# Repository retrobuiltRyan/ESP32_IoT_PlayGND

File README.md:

# ESP32_IoT_PlayGND
Internet of Things + MQTT sensor, input, actuator, motor drive learning board. Can be powered with a power drill battery for immediate remote deployment and sensor monitoring.

Learning Goal: Quick start "how to" develop and build your own IIoT solution with scale and affordability in mind using off-the-shelf hardware and lightweight software.

# Hardware Rev 1.0

| Category       | Components                                                                 |
|----------------|----------------------------------------------------------------------------|
| **Microcontroller** | ESP32-WROOM-32                                                        |
| **Sensors/Input**   | - Temperature & Humidity (SHT45) <br> - Voltage, Current, Power (INA260) <br> - Pushbutton (x4) <br> - Rotary Encoder |
| **Actuators**       | - Relay (10A, 277VAC, 30VDC) <br> - DRV8871 (DC Motor Drive) <br> - A4988 (Stepper Motor Drive) <br> - 4 CH Servo (PCA9685) |
| **Output**          | - RGB LED (x4) <br> - OLED (128x64 pixel) <br> - Buzzer |

ESP-WROOM-32 ESP32: https://www.amazon.com/gp/product/B0D8Q8XFRK/ <br>
USB Drivers for FTDI chips https://docs.espressif.com/projects/esp-idf/en/stable/esp32/get-started/establish-serial-connection.html

BoM
## Bill of Materials (BOM)
| Reference                                                                 | Value                   | Qty | DigiKey P/N               | Adafruit P/N | AliExpress / Amazon Link                                                                 |
|---------------------------------------------------------------------------|-------------------------|-----|---------------------------|--------------|------------------------------------------------------------------------------------------|
| BZ1                                                                       | Buzzer_5V               | 1   | 445-2525-1-ND             |              |                                                                                          |
| C3, C4, C7                                                                | 0.1uF 50V               | 3   | 1276-1068-1-ND            |              |                                                                                          |
| C10, C11                                                                  | 0.22uF 50V CER          | 2   | 445-2283-1-ND             |              |                                                                                          |
| C12, C13, C14                                                             | 22uF 50V                | 3   | 399-11438-1-ND            |              |                                                                                          |
| D2                                                                        | D                       | 1   | S5AC-FDICT-ND             |              |                                                                                          |
| D3, D6, D7, D8                                                            | WS2812B                 | 4   |1568-16347CT-ND            |              |[Aliexpress Link](https://www.aliexpress.us/item/3256802466699315.html)                   |
| D5, D9, D11, D13                                                          | LED, Green              | 3   |1080-1419-1-ND             |              |                                                                                          |
| D10                                                                       | LED Red, 5mm            | 1   | EALP05RDHRA2-ND           |              |                                                                                          |
| D12                                                                       | SMF15A                  | 1   | SMF15A-E3-08CT-ND         |              |                                                                                          |
| D14                                                                       | 1N4148W                 | 1   | 4878-1N4148WCT-ND         |              |                                                                                          |
| J3                                                                        | ServoPort_04            | 1   | S1012EC-40-ND             |              |                                                                                          |
| J5, J8                                                                    | Screw_Terminal_2_P3.50mm| 2   | 732-2747-ND               |              |                                                                                          |
| J7                                                                        | PINHD_2x3_Male          | 1   | S1012EC-40-ND             |              |                                                                                          |
| J15                                                                       | Screw_Terminal_3_P5.00mm| 1   | 277-1578-ND               |              |                                                                                          |
| K1                                                                        | G5Q-1                   | 1   | Z2929-ND                  |              |                                                                                          |
| Q1                                                                        | MOSFET P-CH 30V 25A TO252| 1  | 785-1106-1-ND             |              |                                                                                          |
| Q2, Q3                                                                    | MMBT2222A               | 2   | MMBT2222ATPMSCT-ND        |              |                                                                                          |
| R1, R2, R8, R22, R25, R26, R27, R28, R30, R34, R35, R36, R37, R38         | 10K                     | 14  | 311-10.0KFRCT-ND          |              |                                                                                          |
| R3, R4, R5, R6, R7, R9, R16, R23                                          | 220                     | 8   | 311-220FRCT-ND            |              |                                                                                          |
| R17, R21, R31                                                             | 330                     | 3   | 311-330FRCT-ND            |              |                                                                                          |
| R18, R19, R20, R32                                                        | 1K                      | 4   | 311-1.00KFRCT-ND          |              |                                                                                          |
| R33                                                                       | 100k                    | 1   | 311-100KFRCT-ND           |              |                                                                                          |
| S1                                                                        | SPDT Switch             | 1   | EG5617-ND                 |              |                                                                                          |
| SW1, SW2, SW3, SW4                                                        | Push_Button             | 4   | 2223-TS02-66-60-BK-160-LCR-D-ND |        |                                                                                          |
| SW6                                                                       | RotaryEncoder_Switch_MP | 1   | PEC11R-4220F-S0024-ND     |              |                                                                                          |
| U3                                                                        | PCA9685PW               | 1   | 568-11925-1-ND            |              |                                                                                          |
| U4                                                                        | SHT45                   | 1   |                           | 6174         |                                                                                          |
| U7                                                                        | A4988                   | 1   |                           | 6109         |                                                                                          |
| U8                                                                        | INA260                  | 1   |                           | 4226         |                                                                                          |
| U14                                                                       | MAX40200AUK             | 1   | 175-MAX40203AUK+TCT-ND    |              |                                                                                          |
| U15                                                                       | L7805                   | 1   | 497-7255-1-ND             |              |                                                                                          |
| U18, U19                                                                  | MP1584                  | 2   |                           |              | [AliExpress Link](https://www.aliexpress.us/item/3256806890547813.html)                  |
| U21                                                                       | ESP32                   | 1   |                           |              | [Amazon Link](https://www.amazon.com/gp/product/B0D8Q8XFRK/) _(beware pinout)_            |

## Misc 
Try calling these in a desktop web browser for weather forecast in string format:

*main call*
https://api.weather.gov/points/40.4406,-79.9959

*hourly forecast call*
https://api.weather.gov/gridpoints/PBZ/78,66/forecast/hourly

*weekly forecast*
https://api.weather.gov/gridpoints/PBZ/78,66/forecast

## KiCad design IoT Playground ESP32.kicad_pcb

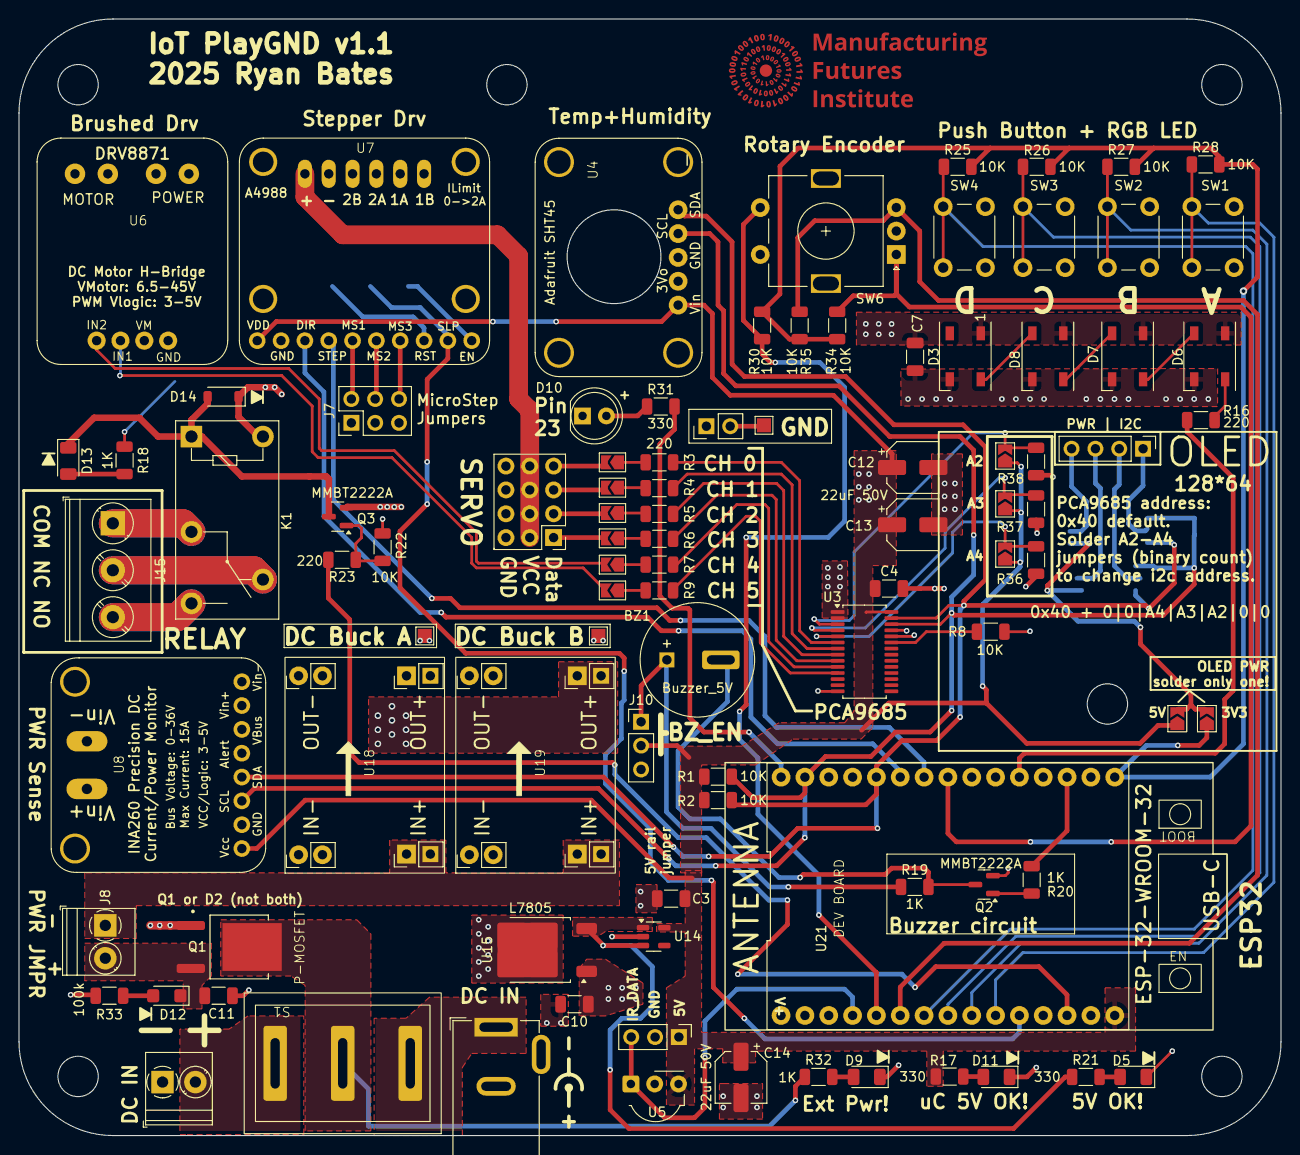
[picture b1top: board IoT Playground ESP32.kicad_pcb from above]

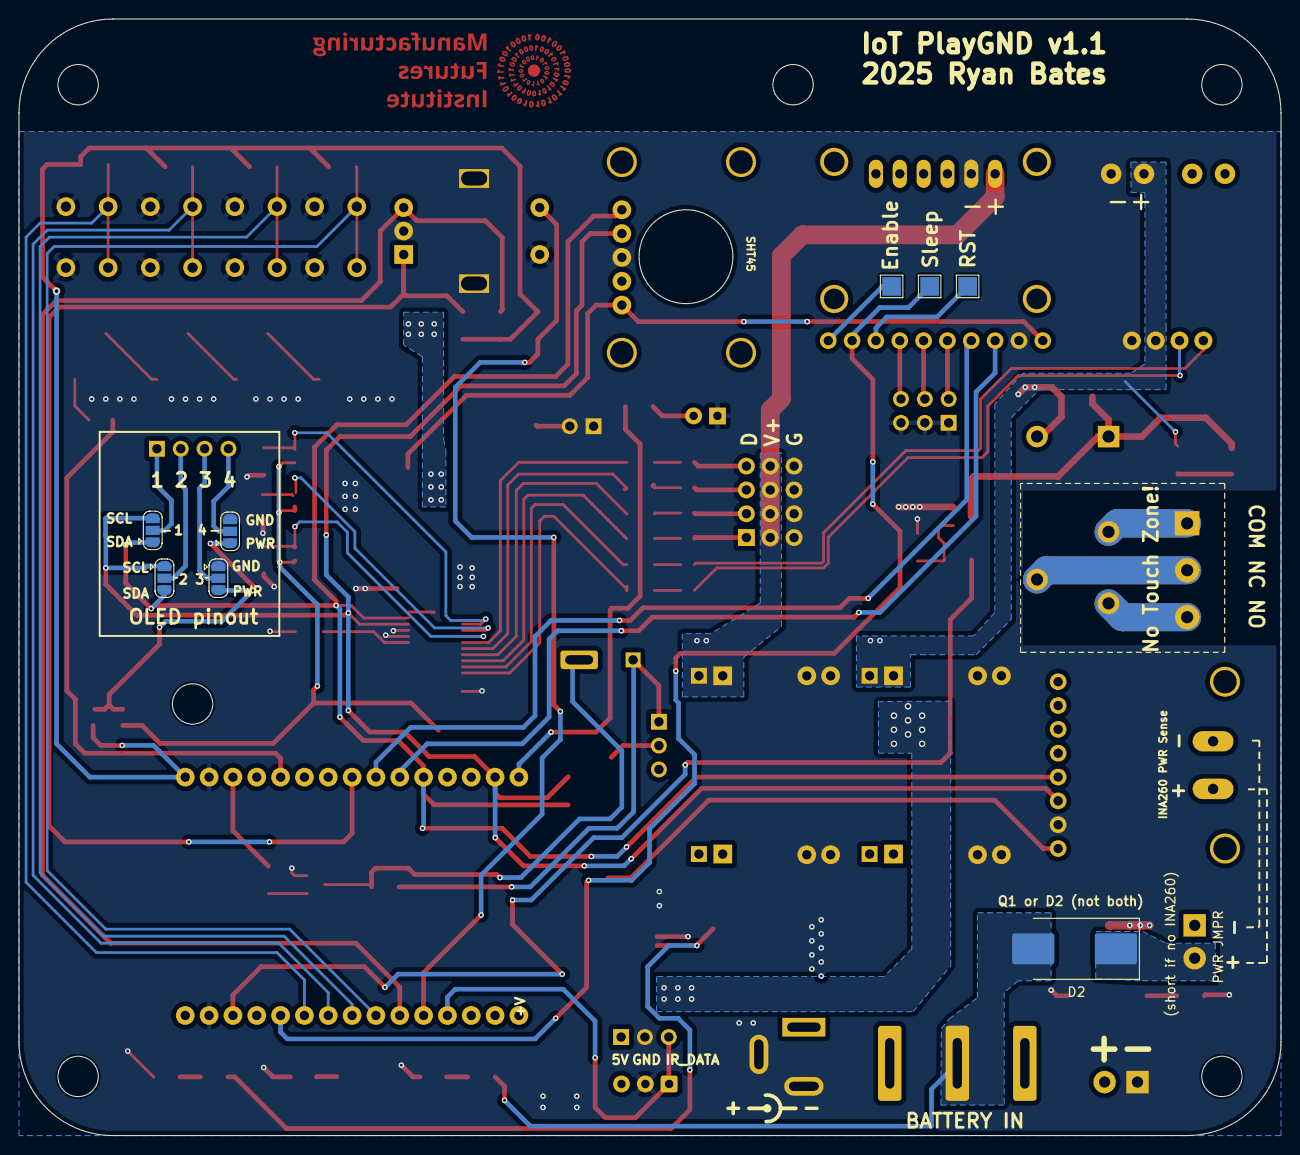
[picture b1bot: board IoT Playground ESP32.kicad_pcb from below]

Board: 2 copper layers, 134.5 x 119.0 mm, 109 parts (8 on the bottom side), 78 nets.

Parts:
BZ1: Buzzer_5V; MagneticBuzzer_ProSignal_ABT-410-RC
C3, C4, C7: 0.1uF 50V; C_1206_3216Metric
C10, C11: 0.22uF 50V CER; C_1206_3216Metric
C12, C13, C14: 22uF 50V; CP_Elec_5x5.3
D2: D; D_SMC_Handsoldering
D3, D6, D7, D8: WS2812B; LED_WS2812B_PLCC4_5.0x5.0mm_P3.2mm
D5, D9, D11, D13: LED; LED_1206_3216Metric
D10: LED; LED_D5.0mm
D12: SMF15A; D_SMF
D14: 1N4148W; D_SOD-123
H1, H2, H3, H4, H5, H6: MountingHole; MountingHole_4.3mm_M4
J1: PINHD_1x2_Male; PinHeader_1x02_P2.54mm_Vertical
J3: ServoPort_04; ServoPort_04_Vertical
J4, J10: PINHD_1x3_Male; PinHeader_1x03_P2.54mm_Vertical
J5, J8: Screw_Terminal_2_P3.50mm; TerminalBlock_Phoenix_PT-1,5-2-3.5-H_1x02_P3.50mm_Horizontal
J6: PINHD_1x4_Male; PinHeader_1x04_P2.54mm_Vertical
J7: PINHD_2x3_Male; PinHeader_2x03_P2.54mm_Vertical
J9: Barrel_Jack; BarrelJack_GCT_DCJ200-10-A_Horizontal
J15: Screw_Terminal_3_P5.00mm; TerminalBlock_Phoenix_PT-1,5-3-5.0-H_1x03_P5.00mm_Horizontal
JP1, JP2, JP3, JP4, JP5, JP6, JP9, JP10, JP13, JP14, JP15: SolderJumper_2_Open; SolderJumper-2_P1.3mm_Open_TrianglePad1.0x1.5mm
JP7, JP8, JP11, JP12: SolderJumper_3_Open; SolderJumper-3_P1.3mm_Open_RoundedPad1.0x1.5mm
K1: G5Q-1; Relay_SPDT_Omron-G5Q-1
Q1: MOSFET P-CH 30V 25A TO252; MOSFET_P-CH_30V_25A_TO252
Q2, Q3: MMBT2222A; SOT-23
R1, R2, R8, R22, R25, R26, R27, R28, R30, R34, R35, R36, R37, R38: 10K; R_1206_3216Metric
R3, R4, R5, R6, R7, R9, R16, R23: 220; R_1206_3216Metric
R17, R21, R31: 330; R_1206_3216Metric
R18, R19, R20, R32: 1K; R_1206_3216Metric
R33: 100k; R_1206_3216Metric
S1: SPDT Switch; SPDT_ Rocker_Switch
SW1, SW2, SW3, SW4: Push_Button; SW_PUSH_6mm
SW6: RotaryEncoder_Switch_MP; RotaryEncoder_Alps_EC11E-Switch_Vertical_H20mm
TP2, TP8, TP9: TestPoint; TestPoint_Pad_2.0x2.0mm
TP10, TP11, TP12: TestPoint; TestPoint_Pad_1.5x1.5mm
U3: PCA9685PW; TSSOP-28_4.4x9.7mm_P0.65mm
U4: SHT45; Adafruit SHT45
U5: TSDP341xx; Vishay_MOLD-3Pin
U6: DRV8871; DRV8871_Adafruit
U7: A4988; Adafruit A4988
U8: INA260; INA260_Adafruit
U14: MAX40200AUK; SOT-23-5
U15: L7805; TO-252-2
U18, U19: MP1584
U21: ESP32; ESP32-WROOM-32_DEV_BOARD

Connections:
5V_IDEAL_DIODE: C3.1, C4.1, C7.1, C12.1, C13.1, C14.1, D3.1 (VDD), D6.1 (VDD), D7.1 (VDD), D8.1 (VDD), J4.1, J10.2, JP9.1 (A), JP13.1 (A), JP14.1 (A), JP15.1 (A), R1.2, R2.2, R17.1, U3.28 (VDD), U4.1 (VIN), U5.3 (Vs), U7.1 (VDD), U8.1 (VCC), U14.5 (OUT), U21.15 (VIN)
+3V3: JP10.1 (A), R25.2, R26.2, R27.2, R28.2, R30.2, R34.2, R35.1, U21.16 (3V3)
+BATT: J9.1, S1.1 (IN_A)
/1: J6.1, JP7.2 (C)
/2: J6.2, JP8.2 (C)
/3: J6.3, JP11.2 (C)
/4: J6.4, JP12.2 (C)
/Button_A: R28.1, SW1.1, U21.10 (D27)
/Button_B: R27.1, SW2.1, U21.9 (D26)
/Button_C: R26.1, SW3.1, U21.8 (D25)
/Button_D: R25.1, SW4.1, U21.7 (D33)
/Buzzer: R20.1, U21.18 (D15)
/DIR Stepper: U7.3 (DIR), U21.25 (D19)
/DRV_A1: JP3.2 (B), U6.2 (IN1)
/DRV_A2: JP2.2 (B), U6.1 (IN2)
/DRV_B1: J3.4 (IN4), JP4.2 (B)
/DRV_C1: J3.3 (IN3), JP5.2 (B)
/DRV_D1: J3.2 (IN2), JP6.2 (B)
/DRV_E1: J3.1 (IN1), JP1.2 (B)
/Enable Stepper: TP2.1, U7.10 (EN)
/Encoder Button: R30.1, SW6.S1, U21.5 (D35)
/Encoder CH_A: R34.1, SW6.A, U21.23 (D5)
/Encoder CH_B: R35.2, SW6.B, U21.6 (D32)
/IR_DATA: J4.3, U5.1 (OUT), U21.4 (D34)
/PWR: JP9.2 (B), JP10.2 (B), JP11.3 (B), JP12.3 (B)
/Power/BATT_IN: D2.2 (A), Q1.2 (S), R32.1, S1.2 (COM)
/Power/RELAY_A_COM: J15.1, K1.2
/Power/VIN: J8.1, U18.3 (IN+), U18.4 (IN+), U19.3 (IN+), U19.4 (IN+)
/RGB_LED: R16.2, U21.20 (D4)
/RST Stepper: TP9.1, U7.8 (RST)
/Relay Signal A: R23.2, U21.13 (D13)
/SCL: JP7.1 (A), JP8.1 (A), R1.1, U3.26 (SCL), U4.4 (SCL), U8.3 (SCL), U21.29 ((SCL)_D22)
/SDA: JP7.3 (B), JP8.3 (B), R2.1, U3.27 (SDA), U4.5 (SDA), U8.4 (SDA), U21.26 ((SDA)_D21)
/Sleep Stepper: TP8.1, U7.9 (SLP), U21.11 (D14)
/Step Stepper: U7.4 (STEP), U21.24 (D18)
GND: C3.2, C4.2, C7.2, C10.2, C11.2, C12.2, C13.2, C14.2, D3.3 (VSS), D5.1 (K), D6.3 (VSS), D7.3 (VSS), D8.3 (VSS), D9.1 (K), D10.1, D11.1 (K), J1.1, J1.2, J3.GND, J4.2, J5.1, J7.1, J7.3, J7.5, J9.2, J9.MP (MountPin), JP11.1 (A), JP12.1 (A), Q1.1 (G), Q2.2 (E), Q3.2 (E), R8.2, R22.1, R33.2, R36.2, R37.2, R38.2, SW1.2, SW2.2, SW3.2, SW4.2, SW6.C, SW6.MP, SW6.S2, TP12.1, U3.1 (A0), U3.2 (A1), U3.14 (VSS), U3.24 (A5), U3.25 (EXTCLK), U4.3 (GND), U5.2 (GND), U6.4 (GND), U6.5 (GND), U7.2 (GND), U7.15 (V-), U8.2 (GND), U14.2 (GND), U15.2 (GND), U18.1 (IN-), U18.2 (IN-), U18.7 (OUT-), U18.8 (OUT-), U19.1 (IN-), U19.2 (IN-), U19.7 (OUT-), U19.8 (OUT-), U21.14 (GND), U21.17 (GND)
unnamed: BZ1.1, J10.1, R19.1
unnamed: D3.4 (DIN), D8.2 (DOUT)
unnamed: D5.2 (A), R21.2
unnamed: D6.4 (DIN), R16.1
unnamed: D6.2 (DOUT), D7.4 (DIN)
unnamed: D7.2 (DOUT), D8.4 (DIN)
unnamed: D9.2 (A), R32.2
unnamed: D10.2, R31.1
unnamed: D11.2 (A), R17.2
unnamed: C11.1, D2.1 (K), D12.1 (A1), J8.2, Q1.3 (D)
unnamed: D12.2 (A2), R33.1
unnamed: D13.2 (A), R18.2
unnamed: D13.1 (K), D14.2 (A), K1.1, Q3.3 (C)
unnamed: J15.2, K1.4
unnamed: J15.3, K1.3
unnamed: JP1.1 (A), R6.1
unnamed: JP2.1 (A), R7.1
unnamed: JP3.1 (A), R9.1
unnamed: JP4.1 (A), R3.1
unnamed: JP5.1 (A), R4.1
unnamed: JP6.1 (A), R5.1
unnamed: JP13.2 (B), R38.1, U3.3 (A2)
unnamed: JP14.2 (B), R37.1, U3.4 (A3)
unnamed: JP15.2 (B), R36.1, U3.5 (A4)
unnamed: Q2.1 (B), R20.2
unnamed: BZ1.2, Q2.3 (C), R19.2
unnamed: Q3.1 (B), R22.2, R23.1
unnamed: J5.2, S1.3 (IN_B)
unnamed: R3.2, U3.6 (LED0)
unnamed: R4.2, U3.7 (LED1)
unnamed: R5.2, U3.8 (LED2)
unnamed: R6.2, U3.9 (LED3)
unnamed: R7.2, U3.10 (LED4)
unnamed: R9.2, U3.11 (LED5)
unnamed: R8.1, U3.23 (~OE)
unnamed: J7.2, U7.5 (MS1)
unnamed: J7.4, U7.6 (MS2)
unnamed: J7.6, U7.7 (MS3)
unnamed: R21.1, U14.1 (VDD), U14.3 (EN), U15.3 (OUT)
unnamed: R31.2, U21.30 (D23)
VOUT_A: D14.1 (K), K1.5, R18.1, TP10.1, U6.3 (VM), U6.6 (VMOTOR), U18.5 (OUT+), U18.6 (OUT+)
VOUT_B: C10.1, J3.VCC, TP11.1, U7.16 (V+), U15.1 (IN), U19.5 (OUT+), U19.6 (OUT+)

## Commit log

2025-07-30 Example Code
    Arduino IDE 2.0+
2025-07-30 Design Files
    kiCAD
2025-08-26 Update 01) ESP32 IoT_PlayGND Blink GPIO23.txt
    fix led variable
2025-08-26 Update 14) ESP32 IoT_PlayGND MQTT w 1.3in OLED.txt
    wifi credentials change
2025-08-26 Update README.md
    details
2025-08-26 Update README.md
    typos, spacing
2025-08-26 example code
2025-08-26 Schematic v1.1 (printable pdf)
2025-08-26 kicad design files v1
    untitled is schematic page 2/2
2025-08-27 Lecture slides
2025-09-11 Update README.md
    led PN
2025-10-17 Create LICENSE
2026-06-10 Update README.md
    ftdi driver link
